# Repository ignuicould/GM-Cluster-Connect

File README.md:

# GM-Cluster-Connect
GM Cluster Connect is a dedicated Raspberry Pi HAT designed for interfacing with and programming automotive EEPROM chips (specifically the M93 series) commonly found in GM instrument clusters.

This project provides a hardware platform and a utility to read full-chip binary dumps and write backups back to new EEPROM chips, allowing for cluster restoration and maintenance.

## Features
* **Dedicated Hardware HAT:** Custom PCB layout for Raspberry Pi featuring:
  * Direct Microwire interfacing via GPIO.
  * Configurable jumper for ORG (mode selection).
  * Decoupling capacitor footprint for signal stability.

* **C++/Python EEPROM Controller:** Command-line utility to:
  * Perform full-chip reads/dumps to .bin files.
  * Flash binary files back to the chip.
  * Support for 8-bit and 16-bit Microwire modes.

## Replacement Chip

https://www.mouser.com/en/ProductDetail/511-M93C56-WMN6TP

https://www.mouser.com/en/ProductDetail/STMicroelectronics/M93C56-RMN3TP-K?qs=4b8myOmUP%252BuoaWIOXeCfgQ%3D%3D (automotive grade)

Datasheet: https://www.st.com/resource/en/datasheet/m93c76-r.pdf

## Hardware Configuration
**WARNING:** This tool interacts with critical vehicle hardware. Ensure all connections are secure before powering the Pi.
* **ORG Jumper:** Set to **GND** for 8-bit operation (default).

## Setup & Installation

### Instrument Cluster
Run the following command to compile cluster.cpp:

```cmd
g++ -o cluster cluster.cpp -lwiringPi -lpthread -lm -lcrypt
```

### Reading Cluster Data
Run the following command to read the data from the EEPROM:

```cmd
sudo ./cluster read
```

### Creating Backup of Cluster Data
Run the following command to make a backup of your current cluster data:

```cmd
sudo ./cluster backup "mycluster.bin"
```

### Writing Backup of Cluster Data to a New Chip
Run the following command to copy your cluster data onto a new chip:

```cmd
sudo ./cluster write "mycluster.bin"
```

### BCM Mileage Calculator
Run the following command to compile mileage.cpp:

```cmd
g++ -O2 -o mileage mileage.cpp
```

### Generating Mileage Hex
The following example assumes 100,000 miles (use your own mileage):

```cmd
./mileage 100,000
```

### Mileage Output (expected)

```cmd
Target Odometer : 100000 miles
Calculated VSS  : 400000000 pulses (0x17d78400)
Encoded Hex     : 17 D7 84 00
BCM 0x0080 Write: 17 D7 84 00 17 D7 84 00 17 D7 84 00
```

### Python approach (not verified working)
Run the following commands on your Raspberry Pi to prepare the environment and enable SPI:

```cmd
sudo apt update && sudo apt install -y python3-pip python3-spidev
sudo raspi-config nonint do_spi 0
sudo reboot
```

## Usage

The eeprom_controller.py script provides a simple CLI interface.

### Dump EEPROM to file

```cmd
python3 eeprom_controller.py --dump backup.bin
```

### Write binary file to EEPROM

```cmd
python3 eeprom_controller.py --write new_data.bin
```

### Help

```cmd
python3 eeprom_controller.py -h
```

## Automotive Safety & Disclaimer
**This project is for educational and maintenance use only.**
* **New Chip Requirement:** This hardware and software are designed for use with **BRAND NEW** EEPROM chips. Attempting to flash data onto a used (worn-out) chip is likely to fail again due to the end-of-life cycle of the original flash memory.
* **Legal:** Modifying odometer data is strictly regulated. Ensure compliance with all local laws and regulations regarding vehicle documentation.
* **Checksums:** Automotive clusters often use checksums or CRCs. Writing raw binary data without calculating or patching the appropriate checksums will likely render the cluster non-functional.
* **Backups:** Always read and save a "Golden Image" (full dump) of your original chip before attempting any write operations.

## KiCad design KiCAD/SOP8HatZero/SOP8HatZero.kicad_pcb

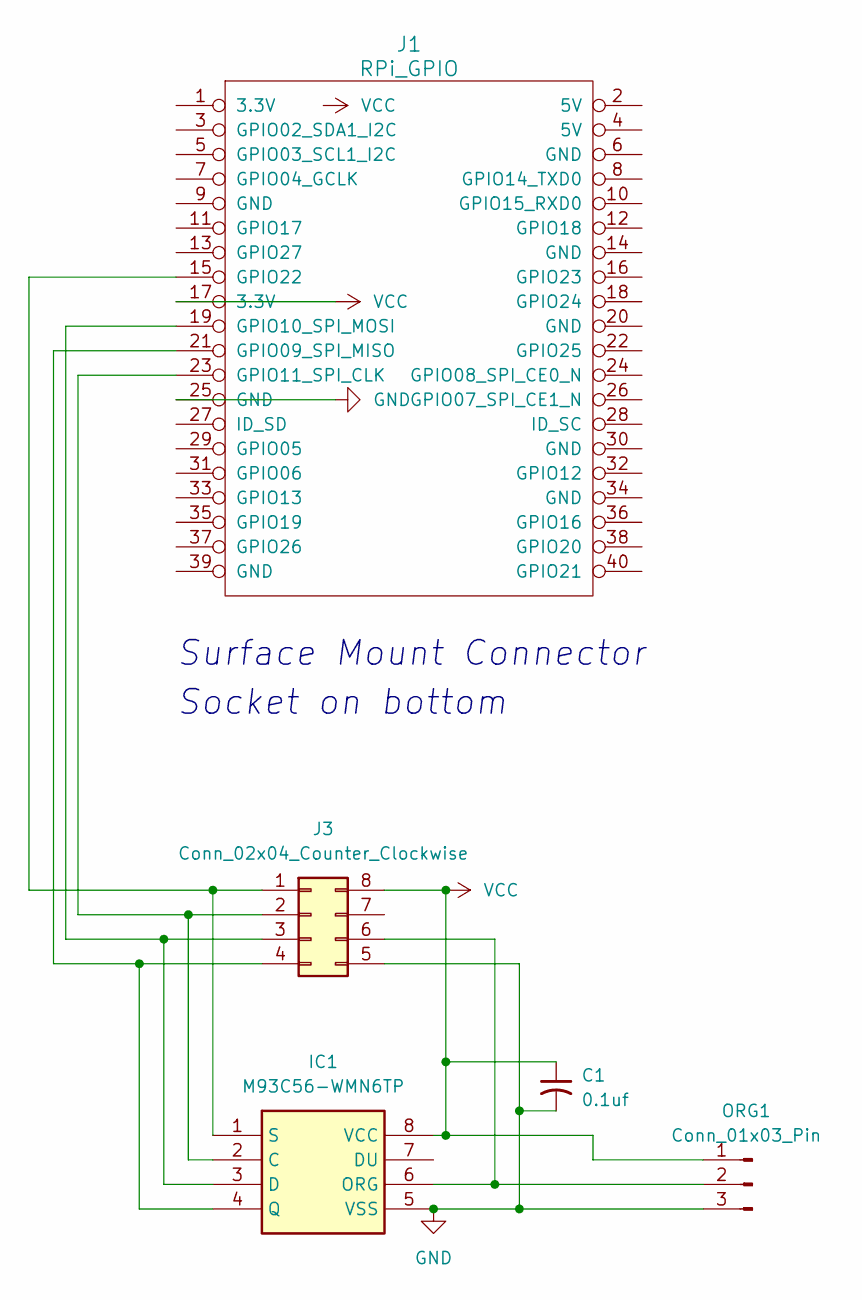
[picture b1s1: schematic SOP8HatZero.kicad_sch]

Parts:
C1: 0.1uf; C_0805_2012Metric_Pad1.18x1.45mm_HandSolder
IC1: M93C56-WMN6TP; SOIC127P600X175-8N; Mouser Part Number 511-M93C56-WMN6TP
J1: RPi_GPIO; Samtec_HLE-120-02-xxx-DV-BE-A_2x20_RPi_Bottom; Mouser Part # 200-HLE12002FDVBEA
J3: Conn_02x04_Counter_Clockwise; PinHeader_2x04_P2.54mm_Vertical
ORG1: Conn_01x03_Pin; PinHeader_1x03_P2.54mm_Vertical

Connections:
GND: C1.2, IC1.5 (VSS), J1.25 (GND), J3.5, ORG1.3
unnamed: IC1.2 (C), J1.23 (GPIO11_SPI_CLK), J3.2
unnamed: IC1.3 (D), J1.19 (GPIO10_SPI_MOSI), J3.3
unnamed: IC1.6 (ORG), J3.6, ORG1.2
unnamed: IC1.4 (Q), J1.21 (GPIO09_SPI_MISO), J3.4
unnamed: IC1.1 (S), J1.15 (GPIO22), J3.1
VCC: C1.1, IC1.8 (VCC), J1.17 (3.3V), J3.8, ORG1.1

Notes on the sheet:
Socket on bottom
Surface Mount Connector

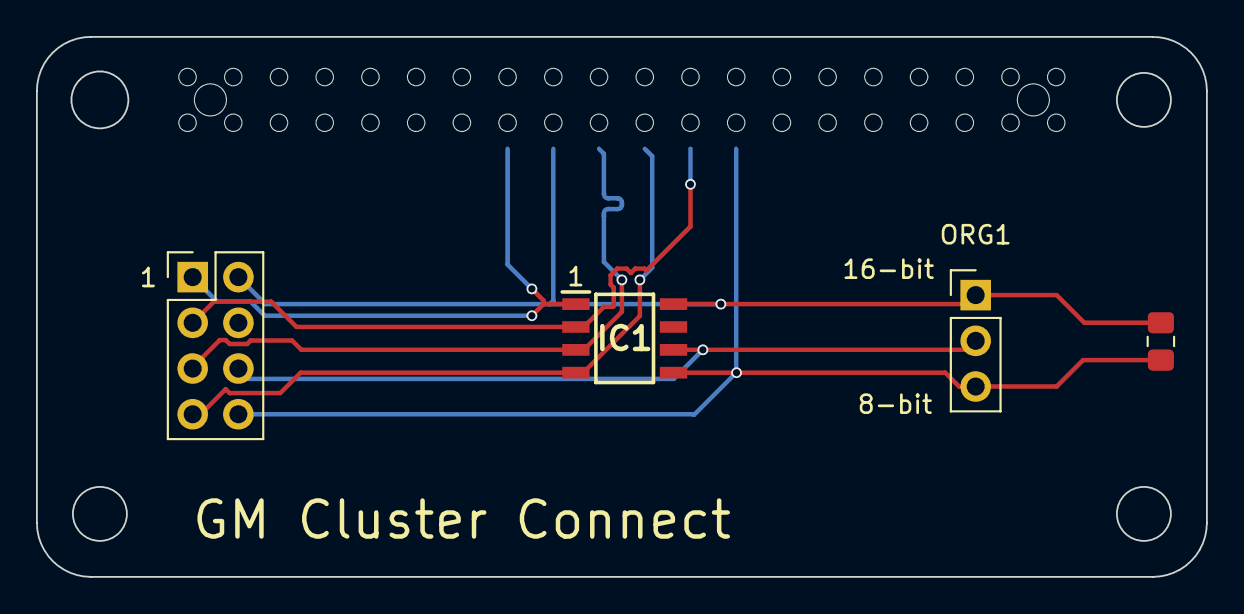
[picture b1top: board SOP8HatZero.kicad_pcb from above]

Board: 2 copper layers, 65.0 x 30.0 mm, 5 parts (1 on the bottom side), 7 nets.

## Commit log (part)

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2026-06-26 Flash Code
    Modifying odometer data is strictly regulated. Ensure compliance with all local laws and regulations regarding vehicle documentation.
2026-06-26 README Update
    **WARNING:** This tool interacts with critical vehicle hardware. Ensure all connections are secure before powering the Pi.
